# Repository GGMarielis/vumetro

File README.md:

# VU Meter Project

This is a **VU Meter** project that uses LEDs to visualize audio signal levels. The project includes schematic designs, PCB layouts, and simulation files.

## Features

- **LED Display**: Shows the audio signal level in real-time.
- **Microcontroller-Based**: Uses a microcontroller for signal processing.
- **Simulation Files**: Includes Proteus 8+ simulation for testing.
- **Eagle PCB Design**: Provides board design files for fabrication.
- **Adjustable Sensitivity**: Can be calibrated for different input signals.

## How It Works

1. The audio signal is taken from an input source.
2. The signal is processed and converted into a corresponding LED display.
3. The brightness and number of LEDs represent the signal intensity.
4. Users can adjust sensitivity to optimize visualization.

## Video Demonstration

Watch the project in action:

## Files Included

- `brd/` - PCB design files (Eagle 7.5+ required)
- `ISIS/` - Simulation files (Proteus 8+ required)
- `src/` - Source code for microcontroller (if applicable)
- `docs/` - Additional documentation

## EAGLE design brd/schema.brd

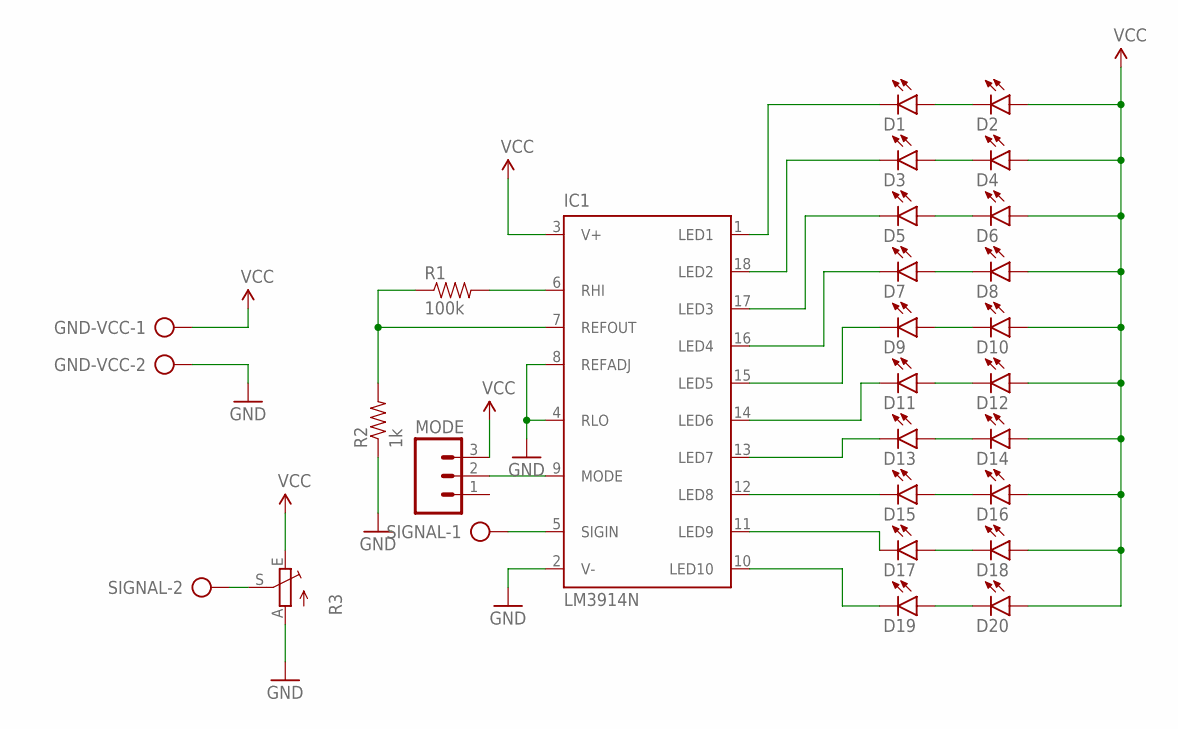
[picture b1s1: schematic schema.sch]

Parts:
D1, D2, D3, D4, D5, D6, D7, D8, D9, D10, D11, D12, D13, D14, D15, D16, D17, D18, D19, D20: LED5MM
GND-VCC: AK500/2
IC1: LM3914N; DIL18
MODE: M03LONGPADS; 1X03_LONGPADS
R1: 100k; AXIAL-0.3-KIT
R2: 1k; AXIAL-0.3-KIT
R3: TRIM_EU-CA14H; CA14H
SIGNAL: AK500/2

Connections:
GND: GND-VCC.2, IC1.2 (V-), IC1.4 (RLO), IC1.8 (REFADJ), R2.P$1 (1), R3.A
unnamed: D1.K (C), IC1.1 (LED1)
unnamed: D3.K (C), IC1.18 (LED2)
unnamed: D5.K (C), IC1.17 (LED3)
unnamed: D7.K (C), IC1.16 (LED4)
unnamed: D9.K (C), IC1.15 (LED5)
unnamed: D11.K (C), IC1.14 (LED6)
unnamed: D13.K (C), IC1.13 (LED7)
unnamed: D15.K (C), IC1.12 (LED8)
unnamed: D17.K (C), IC1.11 (LED9)
unnamed: D19.K (C), IC1.10 (LED10)
unnamed: D1.A, D2.K (C)
unnamed: D3.A, D4.K (C)
unnamed: D5.A, D6.K (C)
unnamed: D7.A, D8.K (C)
unnamed: D9.A, D10.K (C)
unnamed: D11.A, D12.K (C)
unnamed: D13.A, D14.K (C)
unnamed: D15.A, D16.K (C)
unnamed: D17.A, D18.K (C)
unnamed: D19.A, D20.K (C)
unnamed: IC1.6 (RHI), R1.P$2 (2)
unnamed: IC1.7 (REFOUT), R1.P$1 (1), R2.P$2 (2)
unnamed: IC1.9 (MODE), MODE.2
unnamed: IC1.5 (SIGIN), SIGNAL.1
unnamed: R3.S, SIGNAL.2
VCC: D2.A, D4.A, D6.A, D8.A, D10.A, D12.A, D14.A, D16.A, D18.A, D20.A, GND-VCC.1, IC1.3 (V+), MODE.3, R3.E

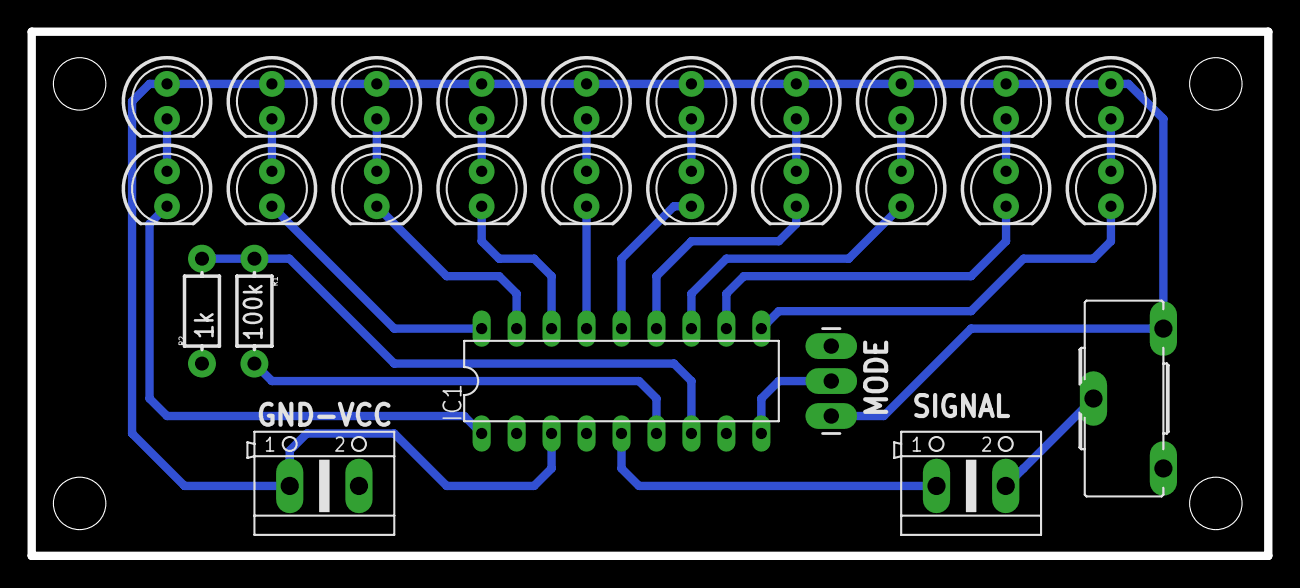
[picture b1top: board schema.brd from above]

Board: 2 copper layers, 89.8 x 38.1 mm, 27 parts (0 on the bottom side), 27 nets.

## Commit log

2020-09-13 fix readme and gitignore
2020-09-13 change readme

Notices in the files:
parts and their libraries:
SparkFun-LED: Licensing: Creative Commons ShareAlike 4.0 International - https://creativecommons.org/licenses/by-sa/4.0
